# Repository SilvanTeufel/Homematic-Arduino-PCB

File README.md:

﻿#### Hobbyists Arduino/Homematic-PCB - designed with KiCad

_designed by Teufel-Engineering - teufel-engineering.com_

- Its a hobbyists Board for Homematic or Other 868 MHZ applications

- This PCB is designed for connecting:
  5V 16M Mini USB Nano V3.0 ATmega328 Micro-controller
  and the:
  CC1101 868MHZ Wireless Module Long Distance Transmission Antenna M115

- You can also Put some Relais on it like:
  Relais SRD-05VDC-SL-C 10A 250VAC Miniatur Print Relais
  to Controll some Lights or sockets.
  or some Infrared LEDs to controll Infrared equipment like your TV

- Connect it with Voltage via:
  Leiterplatten Anschlussklemme Klemmleiste Printklemme Terminal Schraubklemme RM5

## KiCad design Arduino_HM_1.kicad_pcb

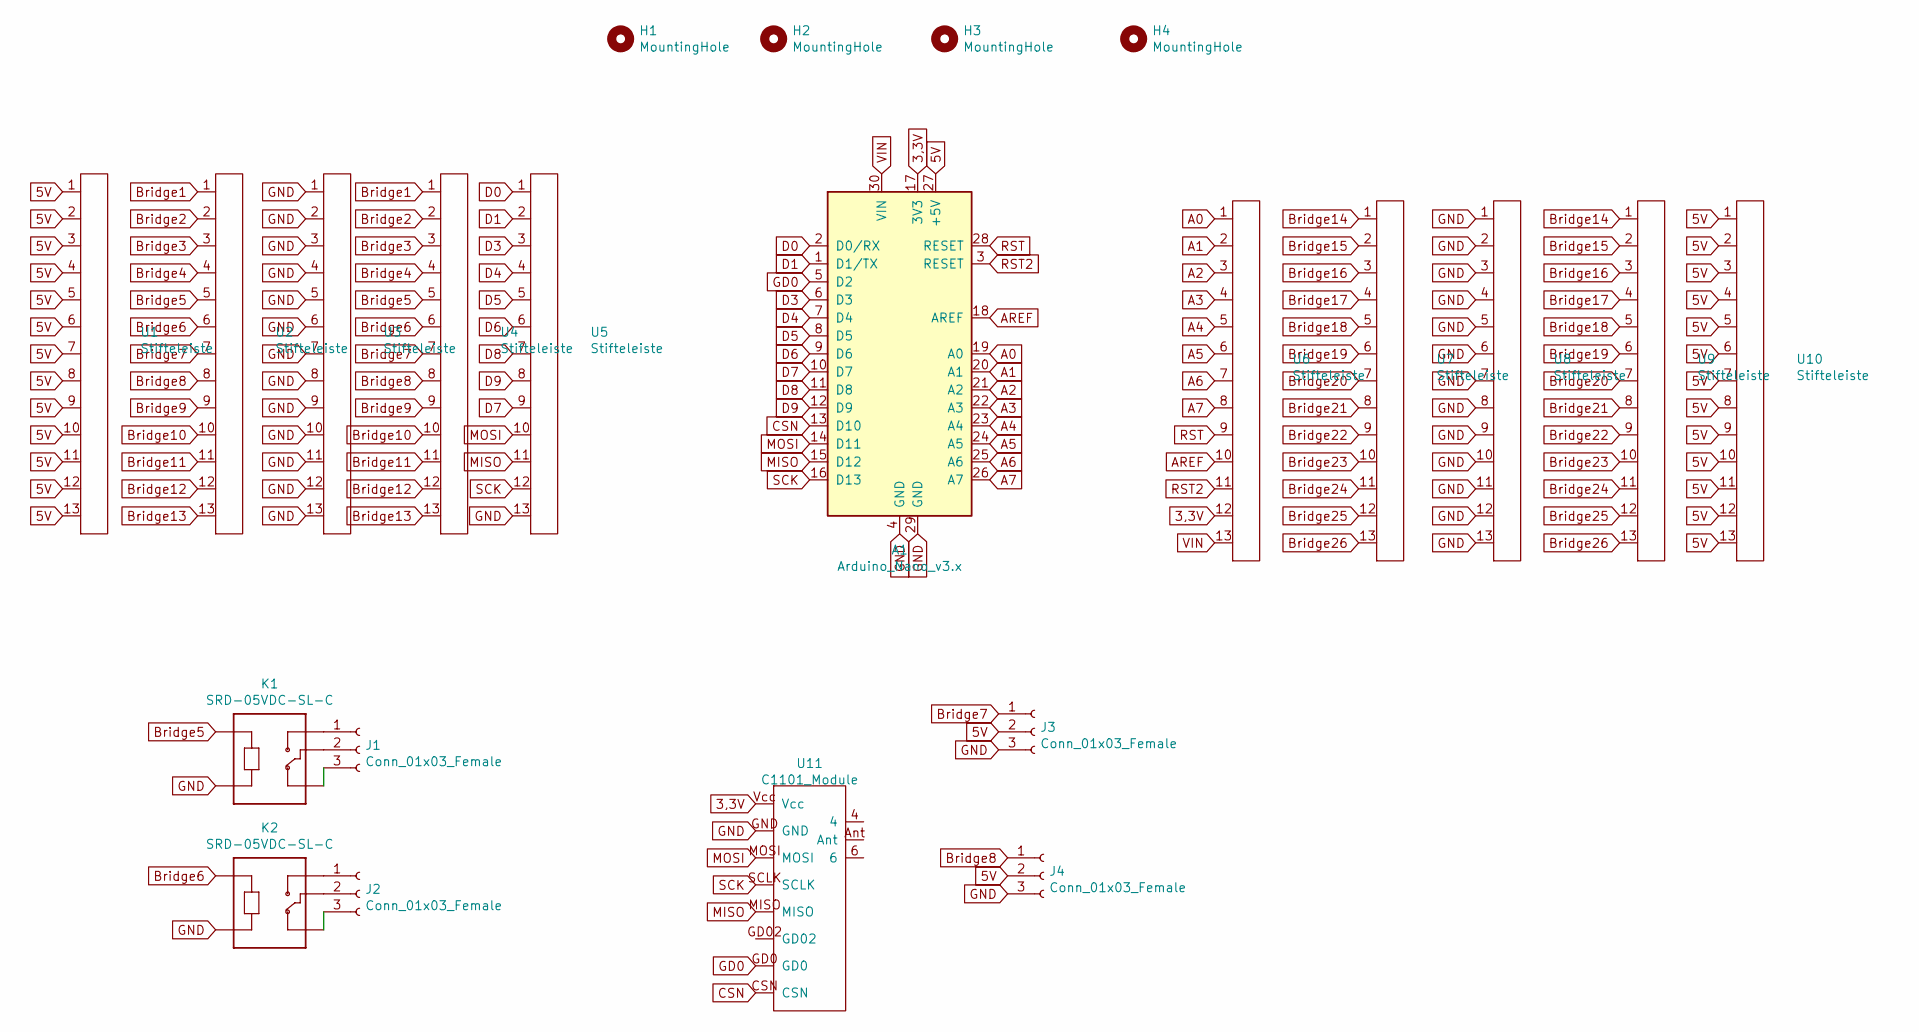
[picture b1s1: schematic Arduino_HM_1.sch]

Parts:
A1: Arduino_Nano_v3.x; Arduino_Nano
H1, H2, H3, H4: MountingHole; MountingHole_2.2mm_M2_DIN965
J1, J2, J3, J4: Conn_01x03_Female; 5_08mm_Klemmleiste
K1, K2: SRD-05VDC-SL-C; RELAY_SRD-05VDC-SL-C
U1, U2, U3, U4, U5, U6, U7, U8, U9, U10: Stifteleiste
U11: C1101_Module; CC1101_modul

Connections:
3,3V: A1.17 (3V3), U6.12, U11.Vcc
5V: A1.27 (+5V), J3.2, J4.2, U1.1, U1.2, U1.3, U1.4, U1.5, U1.6, U1.7, U1.8, U1.9, U1.10, U1.11, U1.12, U1.13, U10.1, U10.2, U10.3, U10.4, U10.5, U10.6, U10.7, U10.8, U10.9, U10.10, U10.11, U10.12, U10.13
A0: A1.19 (A0), U6.1
A1: A1.20 (A1), U6.2
A2: A1.21 (A2), U6.3
A3: A1.22 (A3), U6.4
A4: A1.23 (A4), U6.5
A5: A1.24 (A5), U6.6
A6: A1.25 (A6), U6.7
A7: A1.26 (A7), U6.8
AREF: A1.18 (AREF), U6.10
Bridge1: U2.1, U4.1
Bridge2: U2.2, U4.2
Bridge3: U2.3, U4.3
Bridge4: U2.4, U4.4
Bridge5: K1.A1, U2.5, U4.5
Bridge6: K2.A1, U2.6, U4.6
Bridge7: J3.1, U2.7, U4.7
Bridge8: J4.1, U2.8, U4.8
Bridge9: U2.9, U4.9
Bridge10: U2.10, U4.10
Bridge11: U2.11, U4.11
Bridge12: U2.12, U4.12
Bridge13: U2.13, U4.13
Bridge14: U7.1, U9.1
Bridge15: U7.2, U9.2
Bridge16: U7.3, U9.3
Bridge17: U7.4, U9.4
Bridge18: U7.5, U9.5
Bridge19: U7.6, U9.6
Bridge20: U7.7, U9.7
Bridge21: U7.8, U9.8
Bridge22: U7.9, U9.9
Bridge23: U7.10, U9.10
Bridge24: U7.11, U9.11
Bridge25: U7.12, U9.12
Bridge26: U7.13, U9.13
CSN: A1.13 (D10), U11.CSN
D0: A1.2 (D0/RX), U5.1
D1: A1.1 (D1/TX), U5.2
D3: A1.6 (D3), U5.3
D4: A1.7 (D4), U5.4
D5: A1.8 (D5), U5.5
D6: A1.9 (D6), U5.6
D7: A1.10 (D7), U5.9
D8: A1.11 (D8), U5.7
D9: A1.12 (D9), U5.8
GD0: A1.5 (D2), U11.GD0
GND: A1.4 (GND), A1.29 (GND), J3.3, J4.3, K1.A2, K2.A2, U3.1, U3.2, U3.3, U3.4, U3.5, U3.6, U3.7, U3.8, U3.9, U3.10, U3.11, U3.12, U3.13, U5.13, U8.1, U8.2, U8.3, U8.4, U8.5, U8.6, U8.7, U8.8, U8.9, U8.10, U8.11, U8.12, U8.13, U11.GND
MISO: A1.15 (D12), U5.11, U11.MISO
MOSI: A1.14 (D11), U5.10, U11.MOSI
unnamed: J1.1, K1.NO
unnamed: J1.2, K1.COM
unnamed: J1.3, K1.NC
unnamed: J2.1, K2.NO
unnamed: J2.2, K2.COM
unnamed: J2.3, K2.NC
RST: A1.28 (RESET), U6.9
RST2: A1.3 (RESET), U6.11
SCK: A1.16 (D13), U5.12, U11.SCLK
VIN: A1.30 (VIN), U6.13

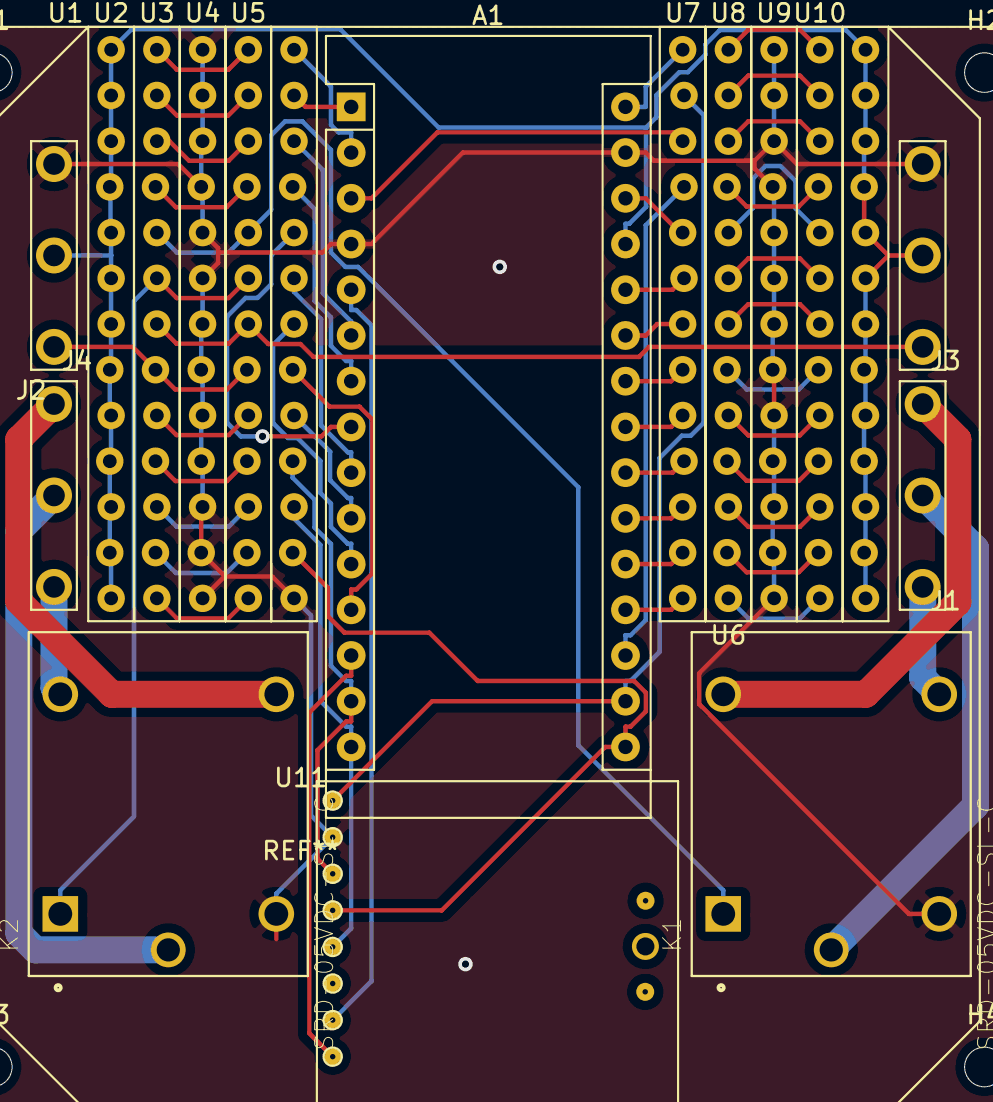
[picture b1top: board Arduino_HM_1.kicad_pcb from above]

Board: 2 copper layers, 22 parts (0 on the bottom side), 61 nets.

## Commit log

2019-11-02 added readme
2019-11-02 changed readme
